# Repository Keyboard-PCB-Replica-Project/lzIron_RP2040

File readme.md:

LZ Iron 레플리카 PCB입니다. 

RGB LED 외의 LED(인디케이터)는 따로 부착해두지 않았습니다.

KT-0805W LED를 구입해서 LED 자리에 납땜해주시면 됩니다. 타오바오나 알리에서 같이 주문해주시면 되며,

납땜 난이도는 스위치보다도 못한 수준입니다.

물론 돈이 더 들어도 괜찮다면, LED까지 부착이 된 채로 배송 오는 옵션을 구현해두겠습니다.

이 기판은 MX 버전이며, ISO 엔터 및 Alps를 지원하지 않습니다!

추후에 추가될 수도 있습니다.

솔더링 버전이며, 아직 제작 후 제대로된 검증이 이뤄지지 않은 상태입니다!

검수는 꼼꼼이 했습니다.

이 기판은 LED와 USB가 전부 기판 전면부에 있기 때문에, 그 외의 SMD 부품들도 전부 전면메 배치했습니다.

간섭은 획인되지 않으나, 폼을 끼우고 빌드할 시 쇼트가 발생할 수 있습니다. 조심해주세요!

그리고 제가 실물 기판이 없어서, 사진을 보고 따 두었습니다.
스위치나 하우징과의 간섭이 없을지 이미지를 보고 잘 확인해보고 주문해주셨으면 해요.
저도 몇번씩 체크했지만 혹시 모르니까 재차 확인 부탁드려요!!

추가 필요 부품 : KT-0805W LED

작동 확인 여부 : 아직 확인되지 않음

----------------------------------------------------------

This is a replica PCB of the LZ Iron.

Indicator LEDs (other than RGB) are not included.

If you want them, you can buy KT-0805W LEDs and solder them yourself.

They’re easy to find on Taobao or AliExpress, and the soldering is even easier than doing switches.

If you're okay with spending a bit more, I might offer a version with the LEDs pre-installed later on.

This PCB supports MX switches only.

It doesn’t support ISO Enter or Alps switches (at least not yet — maybe in the future).

This is a solder-only version, and it hasn’t been fully tested yet.

But I did check everything carefully.

All components, including the LEDs and USB connector, are placed on the front side of the PCB.

Other SMD parts are also on the front.

There shouldn’t be any interference, but if you use case foam, be careful — there’s a chance of shorting.

Extra parts needed: KT-0805W LEDs

Tested and working: Not verified yet

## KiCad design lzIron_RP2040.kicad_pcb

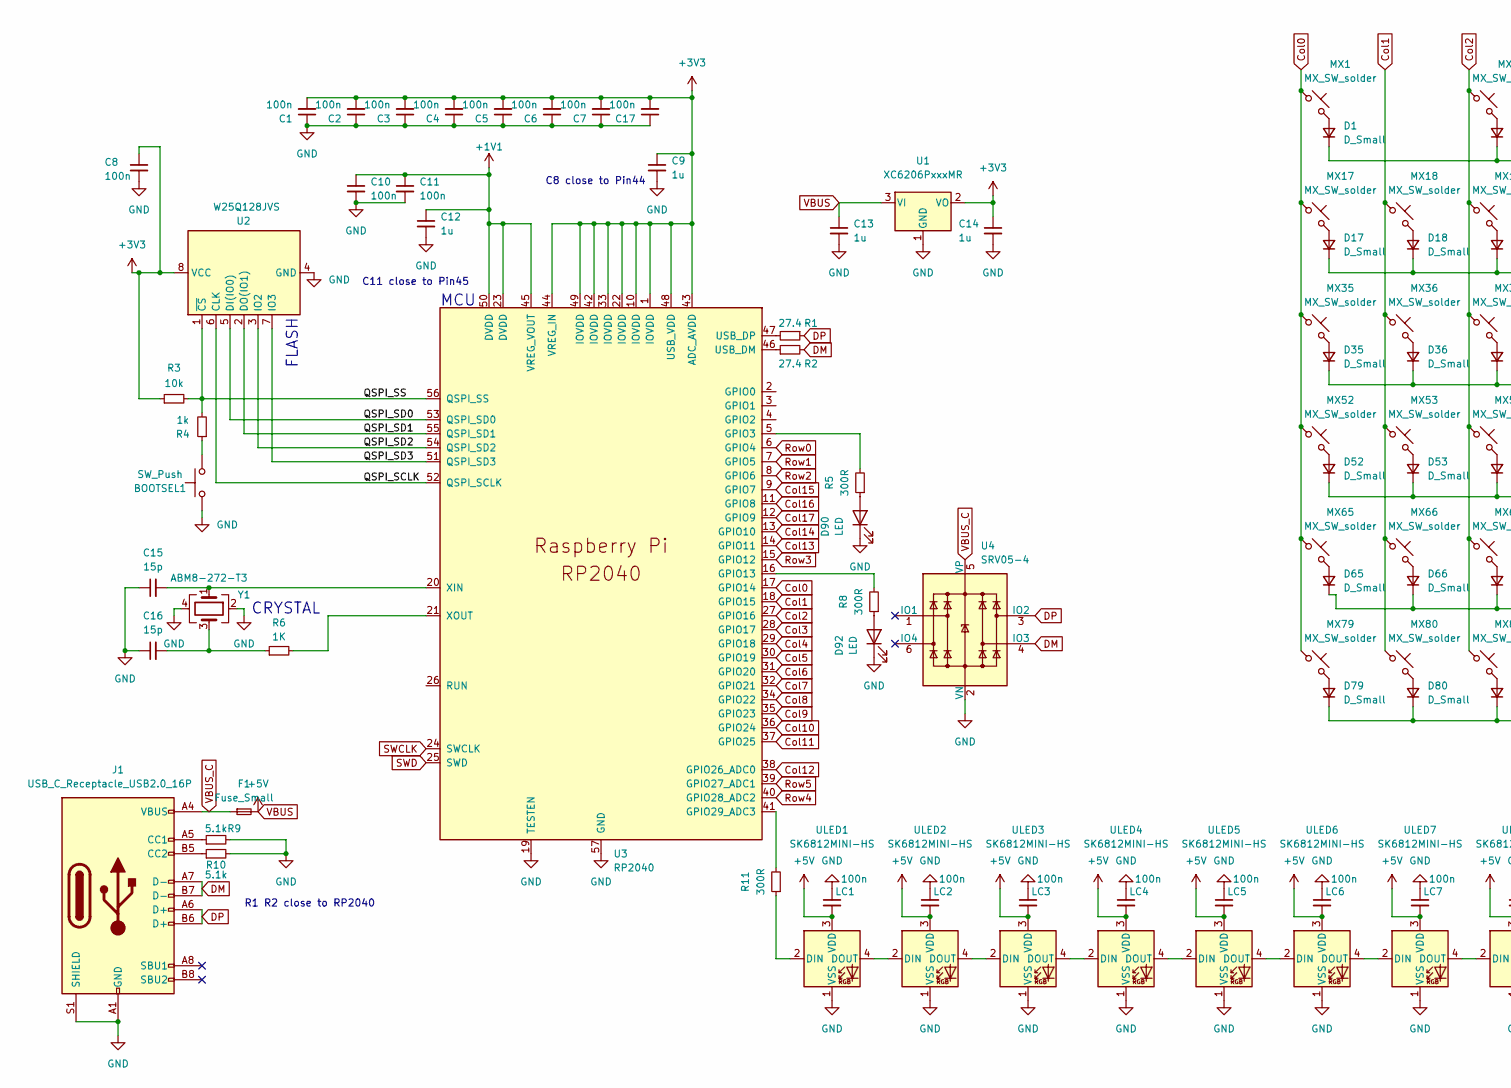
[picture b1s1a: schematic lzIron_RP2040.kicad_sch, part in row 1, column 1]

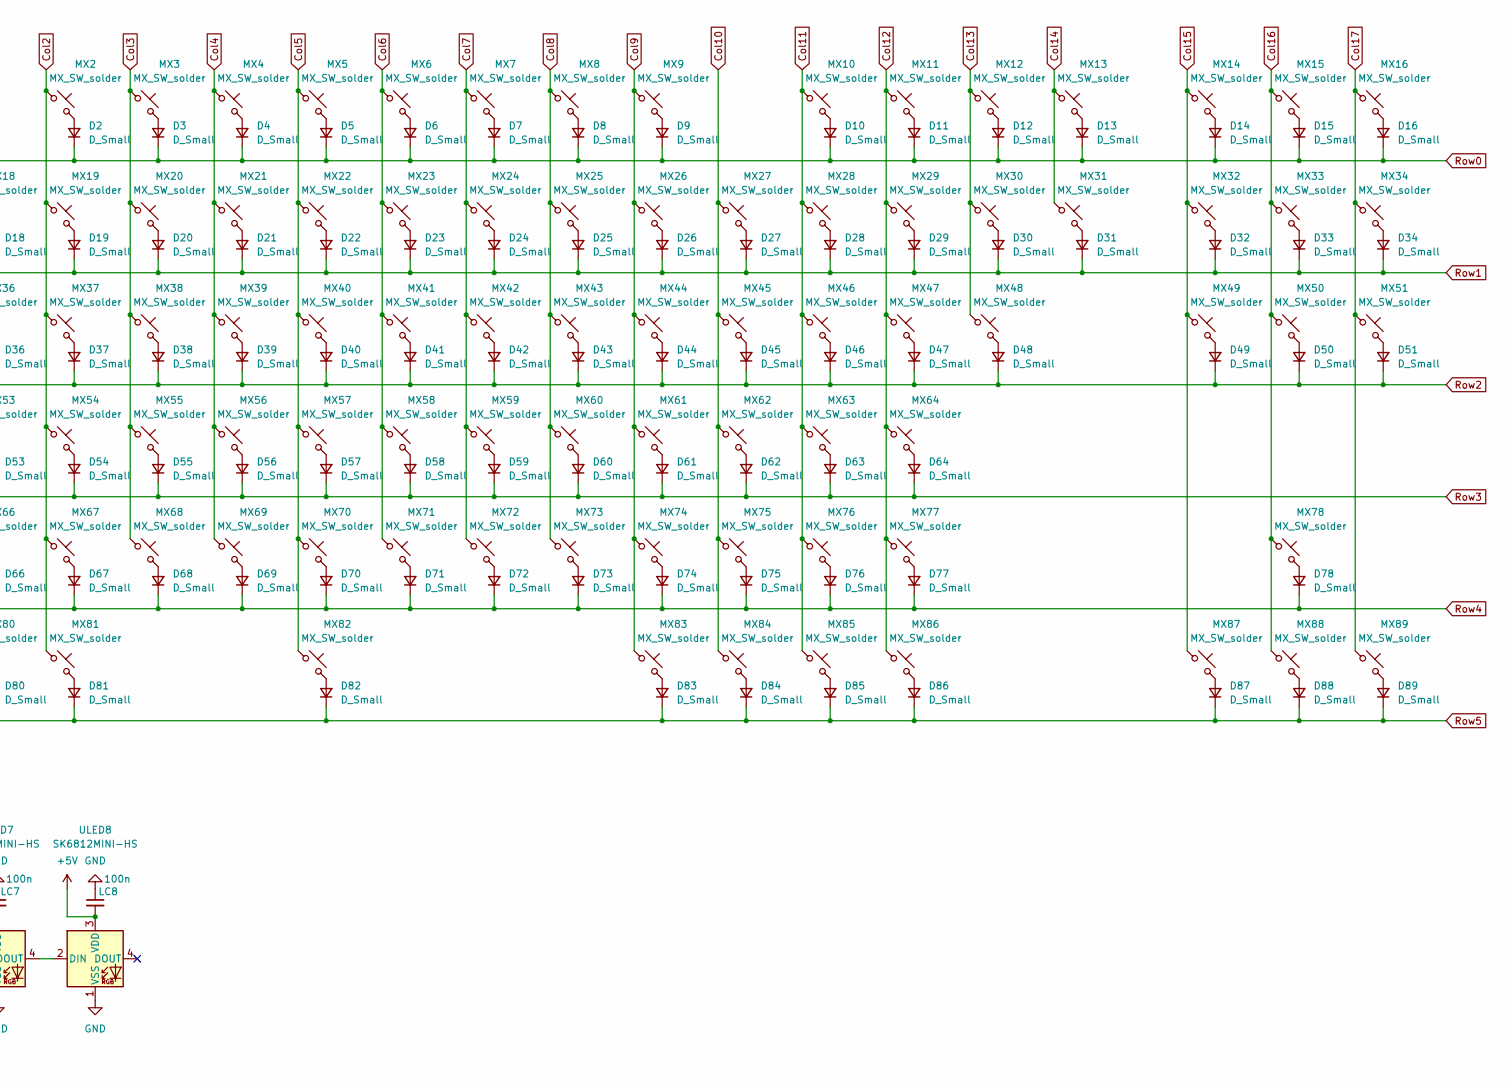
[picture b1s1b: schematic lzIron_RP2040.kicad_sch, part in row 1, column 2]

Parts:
BOOTSEL1: SW_Push; two hole
C1, C2, C3, C4, C5, C6, C7, C8, C10, C11, C17: 100n; C_0402_1005Metric
C9, C12, C13, C14: 1u; C_0402_1005Metric
C15, C16: 15p; C_0402_1005Metric
D1, D2, D3, D4, D5, D6, D7, D8, D9, D10, D11, D12, D13, D14, D15, D16, D17, D18, D19, D20, D21, D22, D23, D24, D25, D26, D27, D28, D29, D30, D31, D32, D33, D34, D35, D36, D37, D38, D39, D40, D41, D42, D43, D44, D45, D46, D47, D48, D49, D50, D51, D52, D53, D54, D55, D56, D57, D58, D59, D60, D61, D62, D63, D64, D65, D66, D67, D68, D69, D70, D71, D72, D73, D74, D75, D76, D77, D78, D79, D80, D81, D82, D83, D84, D85, D86, D87, D88, D89: D_Small; Diode_SOD-123_noref2
D90, D92: LED; KT-0805W
F1: Fuse_Small; Fuse_0805_2012Metric_Pad1.15x1.40mm_HandSolder
J1: USB_C_Receptacle_USB2.0_16P; USB_C_Receptacle_GCT_USB4105-xx-A_16P_TopMnt_Horizontal
LC1, LC2, LC3, LC4, LC5, LC6, LC7, LC8: 100n; C_0402_1005Metric_noref
MX1, MX2, MX3, MX4, MX5, MX6, MX7, MX8, MX9, MX10, MX11, MX12, MX13, MX14, MX15, MX16, MX17, MX18, MX19, MX20, MX21, MX22, MX23, MX24, MX25, MX26, MX27, MX28, MX29, MX30, MX31, MX32, MX33, MX34, MX35, MX36, MX37, MX38, MX39, MX40, MX41, MX42, MX43, MX44, MX45, MX46, MX47, MX48, MX49, MX50, MX51, MX52, MX53, MX54, MX55, MX56, MX57, MX58, MX59, MX60, MX61, MX62, MX63, MX64, MX65, MX66, MX67, MX68, MX69, MX70, MX71, MX72, MX73, MX74, MX75, MX76, MX77, MX78, MX79, MX80, MX81, MX82, MX83, MX84, MX85, MX86, MX87, MX88, MX89: MX_SW_solder; MX_PCB_1.00u_NoSilkscreen3
R1, R2: 27.4; C_0603_1608Metric
R3: 10k; C_0402_1005Metric
R4: 1k; C_0402_1005Metric
R5, R8, R11: 300R; C_0402_1005Metric
R6: 1K; C_0402_1005Metric
R9, R10: 5.1k; C_0402_1005Metric
U1: XC6206PxxxMR; SOT-23
U2: W25Q128JVS; SOIC-8_5.23x5.23mm_P1.27mm
U3: RP2040; RP2040-QFN-56
U4: SRV05-4; SOT-23-6
ULED1, ULED2, ULED3, ULED4, ULED5, ULED6, ULED7, ULED8: SK6812MINI-HS; LED_SK6812MINI_PLCC4_3.5x3.5mm_P1.75mm_2
Y1: ABM8-272-T3; Oscillator_SMD_EuroQuartz_XO32-4Pin_3.2x2.5mm

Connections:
+1V1: C10.1, C11.1, C12.1, U3.23 (DVDD), U3.45 (VREG_VOUT), U3.50 (DVDD)
+3V3: C1.2, C2.2, C3.2, C4.2, C5.2, C6.2, C7.2, C8.1, C9.1, C14.1, C17.2, R3.1, U1.2 (VO), U2.8 (VCC), U3.1 (IOVDD), U3.10 (IOVDD), U3.22 (IOVDD), U3.33 (IOVDD), U3.42 (IOVDD), U3.43 (ADC_AVDD), U3.44 (VREG_IN), U3.48 (USB_VDD), U3.49 (IOVDD)
/QSPI_SCLK: U2.6 (CLK), U3.52 (QSPI_SCLK)
/QSPI_SD0: U2.5 (DI(IO0)), U3.53 (QSPI_SD0)
/QSPI_SD1: U2.2 (DO(IO1)), U3.55 (QSPI_SD1)
/QSPI_SD2: U2.3 (IO2), U3.54 (QSPI_SD2)
/QSPI_SD3: U2.7 (IO3), U3.51 (QSPI_SD3)
/QSPI_SS: R3.2, R4.2, U2.1 (~CS), U3.56 (QSPI_SS)
Col0: MX1.1, MX17.1, MX35.1, MX52.1, MX65.1, MX79.1, U3.17 (GPIO14)
Col1: MX18.1, MX36.1, MX53.1, MX66.1, MX80.1, U3.18 (GPIO15)
Col2: MX2.1, MX19.1, MX37.1, MX54.1, MX67.1, MX81.1, U3.27 (GPIO16)
Col3: MX3.1, MX20.1, MX38.1, MX55.1, MX68.1, U3.28 (GPIO17)
Col4: MX4.1, MX21.1, MX39.1, MX56.1, MX69.1, U3.29 (GPIO18)
Col5: MX5.1, MX22.1, MX40.1, MX57.1, MX70.1, MX82.1, U3.30 (GPIO19)
Col6: MX6.1, MX23.1, MX41.1, MX58.1, MX71.1, U3.31 (GPIO20)
Col7: MX7.1, MX24.1, MX42.1, MX59.1, MX72.1, U3.32 (GPIO21)
Col8: MX8.1, MX25.1, MX43.1, MX60.1, MX73.1, U3.34 (GPIO22)
Col9: MX9.1, MX26.1, MX44.1, MX61.1, MX74.1, MX83.1, U3.35 (GPIO23)
Col10: MX27.1, MX45.1, MX62.1, MX75.1, MX84.1, U3.36 (GPIO24)
Col11: MX10.1, MX28.1, MX46.1, MX63.1, MX76.1, MX85.1, U3.37 (GPIO25)
Col12: MX11.1, MX29.1, MX47.1, MX64.1, MX77.1, MX86.1, U3.38 (GPIO26_ADC0)
Col13: MX12.1, MX30.1, MX48.1, U3.14 (GPIO11)
Col14: MX13.1, MX31.1, U3.13 (GPIO10)
Col15: MX14.1, MX32.1, MX49.1, MX87.1, U3.9 (GPIO7)
Col16: MX15.1, MX33.1, MX50.1, MX78.1, MX88.1, U3.11 (GPIO8)
Col17: MX16.1, MX34.1, MX51.1, MX89.1, U3.12 (GPIO9)
DM: J1.A7 (D-), J1.B7 (D-), R2.2, U4.4 (IO3)
DP: J1.A6 (D+), J1.B6 (D+), R1.1, U4.3 (IO2)
GND: BOOTSEL1.1, C1.1, C2.1, C3.1, C4.1, C5.1, C6.1, C7.1, C8.2, C9.2, C10.2, C11.2, C12.2, C13.2, C14.2, C15.1, C16.1, C17.1, D90.1 (K), D92.1 (K), J1.A1 (GND), J1.A12 (GND), J1.B1 (GND), J1.B12 (GND), J1.S1 (SHIELD), LC1.1, LC2.1, LC3.1, LC4.1, LC5.1, LC6.1, LC7.1, LC8.1, R9.2, R10.2, U1.1 (GND), U2.4 (GND), U3.19 (TESTEN), U3.57 (GND), U4.2 (VN), ULED1.1 (VSS), ULED2.1 (VSS), ULED3.1 (VSS), ULED4.1 (VSS), ULED5.1 (VSS), ULED6.1 (VSS), ULED7.1 (VSS), ULED8.1 (VSS), Y1.2, Y1.4
unnamed: BOOTSEL1.2, R4.1
unnamed: C16.2, R6.1, Y1.3
unnamed: D1.2 (A), MX1.2
unnamed: D2.2 (A), MX2.2
unnamed: D3.2 (A), MX3.2
unnamed: D4.2 (A), MX4.2
unnamed: D5.2 (A), MX5.2
unnamed: D6.2 (A), MX6.2
unnamed: D7.2 (A), MX7.2
unnamed: D8.2 (A), MX8.2
unnamed: D9.2 (A), MX9.2
unnamed: D10.2 (A), MX10.2
unnamed: D11.2 (A), MX11.2
unnamed: D12.2 (A), MX12.2
unnamed: D13.2 (A), MX13.2
unnamed: D14.2 (A), MX14.2
unnamed: D15.2 (A), MX15.2
unnamed: D16.2 (A), MX16.2
unnamed: D17.2 (A), MX17.2
unnamed: D18.2 (A), MX18.2
unnamed: D19.2 (A), MX19.2
unnamed: D20.2 (A), MX20.2
unnamed: D21.2 (A), MX21.2
unnamed: D22.2 (A), MX22.2
unnamed: D23.2 (A), MX23.2
unnamed: D24.2 (A), MX24.2
unnamed: D25.2 (A), MX25.2
unnamed: D26.2 (A), MX26.2
unnamed: D27.2 (A), MX27.2
unnamed: D28.2 (A), MX28.2
unnamed: D29.2 (A), MX29.2
unnamed: D30.2 (A), MX30.2
unnamed: D31.2 (A), MX31.2
unnamed: D32.2 (A), MX32.2
unnamed: D33.2 (A), MX33.2
unnamed: D34.2 (A), MX34.2
unnamed: D35.2 (A), MX35.2
unnamed: D36.2 (A), MX36.2
unnamed: D37.2 (A), MX37.2
unnamed: D38.2 (A), MX38.2
unnamed: D39.2 (A), MX39.2
unnamed: D40.2 (A), MX40.2
unnamed: D41.2 (A), MX41.2
unnamed: D42.2 (A), MX42.2
unnamed: D43.2 (A), MX43.2
unnamed: D44.2 (A), MX44.2
unnamed: D45.2 (A), MX45.2
unnamed: D46.2 (A), MX46.2
unnamed: D47.2 (A), MX47.2
unnamed: D48.2 (A), MX48.2
unnamed: D49.2 (A), MX49.2
unnamed: D50.2 (A), MX50.2
unnamed: D51.2 (A), MX51.2
unnamed: D52.2 (A), MX52.2
unnamed: D53.2 (A), MX53.2
unnamed: D54.2 (A), MX54.2
unnamed: D55.2 (A), MX55.2
unnamed: D56.2 (A), MX56.2
unnamed: D57.2 (A), MX57.2
unnamed: D58.2 (A), MX58.2
unnamed: D59.2 (A), MX59.2
unnamed: D60.2 (A), MX60.2
unnamed: D61.2 (A), MX61.2
unnamed: D62.2 (A), MX62.2
unnamed: D63.2 (A), MX63.2
unnamed: D64.2 (A), MX64.2
unnamed: D65.2 (A), MX65.2
unnamed: D66.2 (A), MX66.2
unnamed: D67.2 (A), MX67.2
unnamed: D68.2 (A), MX68.2
unnamed: D69.2 (A), MX69.2
unnamed: D70.2 (A), MX70.2
unnamed: D71.2 (A), MX71.2
unnamed: D72.2 (A), MX72.2
unnamed: D73.2 (A), MX73.2
unnamed: D74.2 (A), MX74.2
unnamed: D75.2 (A), MX75.2
unnamed: D76.2 (A), MX76.2
unnamed: D77.2 (A), MX77.2
unnamed: D78.2 (A), MX78.2
unnamed: D79.2 (A), MX79.2
unnamed: D80.2 (A), MX80.2
unnamed: D81.2 (A), MX81.2
unnamed: D82.2 (A), MX82.2
unnamed: D83.2 (A), MX83.2
unnamed: D84.2 (A), MX84.2
unnamed: D85.2 (A), MX85.2
unnamed: D86.2 (A), MX86.2
unnamed: D87.2 (A), MX87.2
unnamed: D88.2 (A), MX88.2
unnamed: D89.2 (A), MX89.2
unnamed: D90.2 (A), R5.1
unnamed: D92.2 (A), R8.1
unnamed: J1.A5 (CC1), R9.1
unnamed: J1.B5 (CC2), R10.1
unnamed: R5.2, U3.5 (GPIO3)
unnamed: R8.2, U3.16 (GPIO13)
unnamed: R11.2, U3.41 (GPIO29_ADC3)
unnamed: R2.1, U3.46 (USB_DM)
unnamed: R1.2, U3.47 (USB_DP)
unnamed: C15.2, U3.20 (XIN), Y1.1
unnamed: R6.2, U3.21 (XOUT)
unnamed: R11.1, ULED1.2 (DIN)
unnamed: ULED1.4 (DOUT), ULED2.2 (DIN)
unnamed: ULED2.4 (DOUT), ULED3.2 (DIN)
unnamed: ULED3.4 (DOUT), ULED4.2 (DIN)
unnamed: ULED4.4 (DOUT), ULED5.2 (DIN)
unnamed: ULED5.4 (DOUT), ULED6.2 (DIN)
unnamed: ULED6.4 (DOUT), ULED7.2 (DIN)
unnamed: ULED7.4 (DOUT), ULED8.2 (DIN)
Row0: D1.1 (K), D2.1 (K), D3.1 (K), D4.1 (K), D5.1 (K), D6.1 (K), D7.1 (K), D8.1 (K), D9.1 (K), D10.1 (K), D11.1 (K), D12.1 (K), D13.1 (K), D14.1 (K), D15.1 (K), D16.1 (K), U3.6 (GPIO4)
Row1: D17.1 (K), D18.1 (K), D19.1 (K), D20.1 (K), D21.1 (K), D22.1 (K), D23.1 (K), D24.1 (K), D25.1 (K), D26.1 (K), D27.1 (K), D28.1 (K), D29.1 (K), D30.1 (K), D31.1 (K), D32.1 (K), D33.1 (K), D34.1 (K), U3.7 (GPIO5)
Row2: D35.1 (K), D36.1 (K), D37.1 (K), D38.1 (K), D39.1 (K), D40.1 (K), D41.1 (K), D42.1 (K), D43.1 (K), D44.1 (K), D45.1 (K), D46.1 (K), D47.1 (K), D48.1 (K), D49.1 (K), D50.1 (K), D51.1 (K), U3.8 (GPIO6)
Row3: D52.1 (K), D53.1 (K), D54.1 (K), D55.1 (K), D56.1 (K), D57.1 (K), D58.1 (K), D59.1 (K), D60.1 (K), D61.1 (K), D62.1 (K), D63.1 (K), D64.1 (K), U3.15 (GPIO12)
Row4: D65.1 (K), D66.1 (K), D67.1 (K), D68.1 (K), D69.1 (K), D70.1 (K), D71.1 (K), D72.1 (K), D73.1 (K), D74.1 (K), D75.1 (K), D76.1 (K), D77.1 (K), D78.1 (K), U3.40 (GPIO28_ADC2)
Row5: D79.1 (K), D80.1 (K), D81.1 (K), D82.1 (K), D83.1 (K), D84.1 (K), D85.1 (K), D86.1 (K), D87.1 (K), D88.1 (K), D89.1 (K), U3.39 (GPIO27_ADC1)
SWCLK: U3.24 (SWCLK)
SWD: U3.25 (SWD)
VBUS: C13.1, F1.2, LC1.2, LC2.2, LC3.2, LC4.2, LC5.2, LC6.2, LC7.2, LC8.2, U1.3 (VI), ULED1.3 (VDD), ULED2.3 (VDD), ULED3.3 (VDD), ULED4.3 (VDD), ULED5.3 (VDD), ULED6.3 (VDD), ULED7.3 (VDD), ULED8.3 (VDD)
VBUS_C: F1.1, J1.A4 (VBUS), J1.A9 (VBUS), J1.B4 (VBUS), J1.B9 (VBUS), U4.5 (VP)

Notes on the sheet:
MCU
FLASH
R1 R2 close to RP2040
C8 close to Pin44
CRYSTAL
C11 close to Pin45

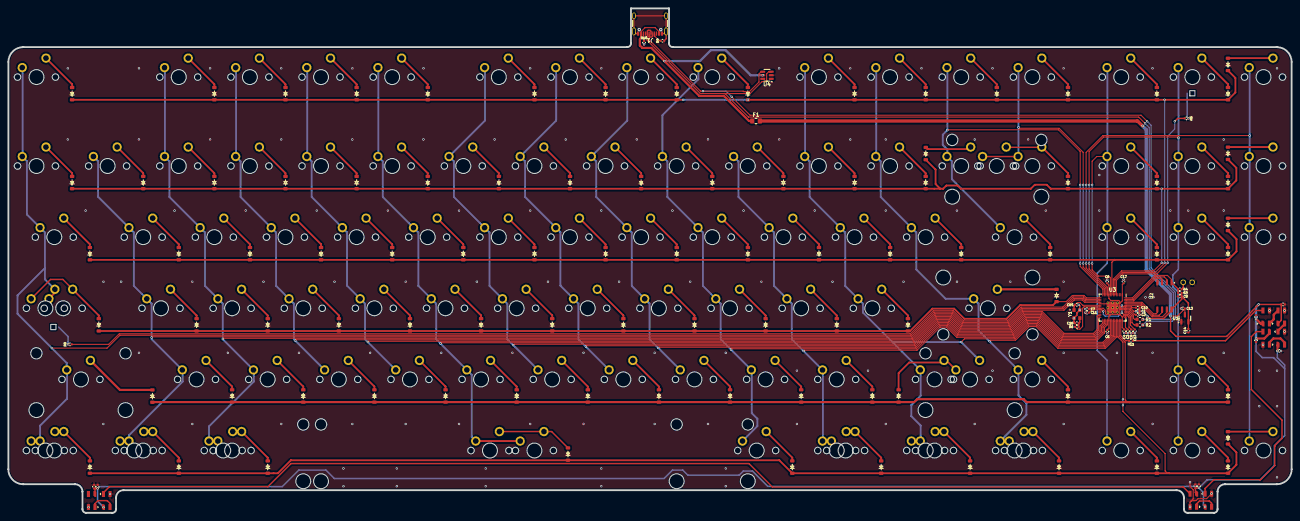
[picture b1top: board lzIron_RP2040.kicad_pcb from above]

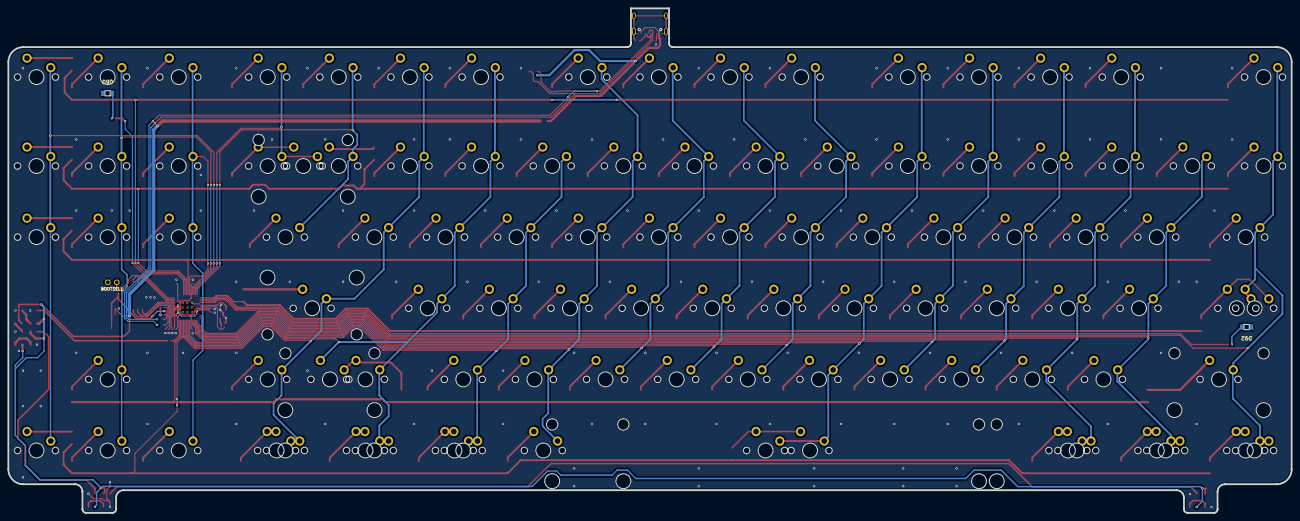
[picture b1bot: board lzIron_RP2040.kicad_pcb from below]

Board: 2 copper layers, 343.7 x 135.1 mm, 231 parts (2 on the bottom side), 147 nets.

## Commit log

2025-07-03 V1.0
2025-07-04 V1.1
2025-07-07 V1.2
2025-07-12 V1.3
